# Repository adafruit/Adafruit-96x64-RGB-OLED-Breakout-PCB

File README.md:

# PCB for the Adafruit Mini Color OLED breakout board

<a href="http://www.adafruit.com/products/684"><br/>Click here to purchase one from the Adafruit shop</a>

We love our black and white monochrome displays but we also like to dabble with some color now and then. Our new 0.96" color OLED displays are perfect when you need an ultra-small display with vivid, high-contrast 16-bit color. The visible portion of the OLED measures 0.96" diagonal and contains 96x64 RGB pixels, each one made of red, green and blue OLEDs. Each pixel can be set with 16-bits of resolution for a large range of colors. Because the display uses OLEDs, there is no backlight, and the contrast is very high (black is really black). We picked this display for its excellent color, this is the nicest mini OLED we could find!

This OLED uses the SSD1331 driver chip, which manages the display. You can talk to the driver chip using either 4-wire write-only SPI (clock, data, chip select, data/command and an optional reset pin). Included on the fully assembled breakout is the OLED display and a small boost converter (required for providing 12V to the OLED) and a microSD card holder. New! We've updated this design to have built-in logic level shifting so you can use it with 3-5VDC power and logic levels. Our example code shows how to read a bitmap from the uSD card and display it all via SPI.

Of course, we wouldn't just leave you with a datasheet and a "good luck!" - [ we've written a full open source graphics library that can draw pixels, lines, rectangles, circles, text and bitmaps as well as example code and a wiring tutorial](http://learn.adafruit.com/096-mini-color-oled).
The code is written for Arduino but can be easily ported to your favorite microcontroller!

OLED Breakout Board - 16-bit Color 0.96" w/microSD holder ([4:55](https://www.youtube.com/watch?feature=player_detailpage&v=Cvf2_pIx7Aw#t=295))

## License

Adafruit invests time and resources providing this open source design, 
please support Adafruit and open-source hardware by purchasing 
products from Adafruit!

Designed by Adafruit Industries.  
Creative Commons Attribution, Share-Alike license, check license.txt for more information
All text above must be included in any redistribution

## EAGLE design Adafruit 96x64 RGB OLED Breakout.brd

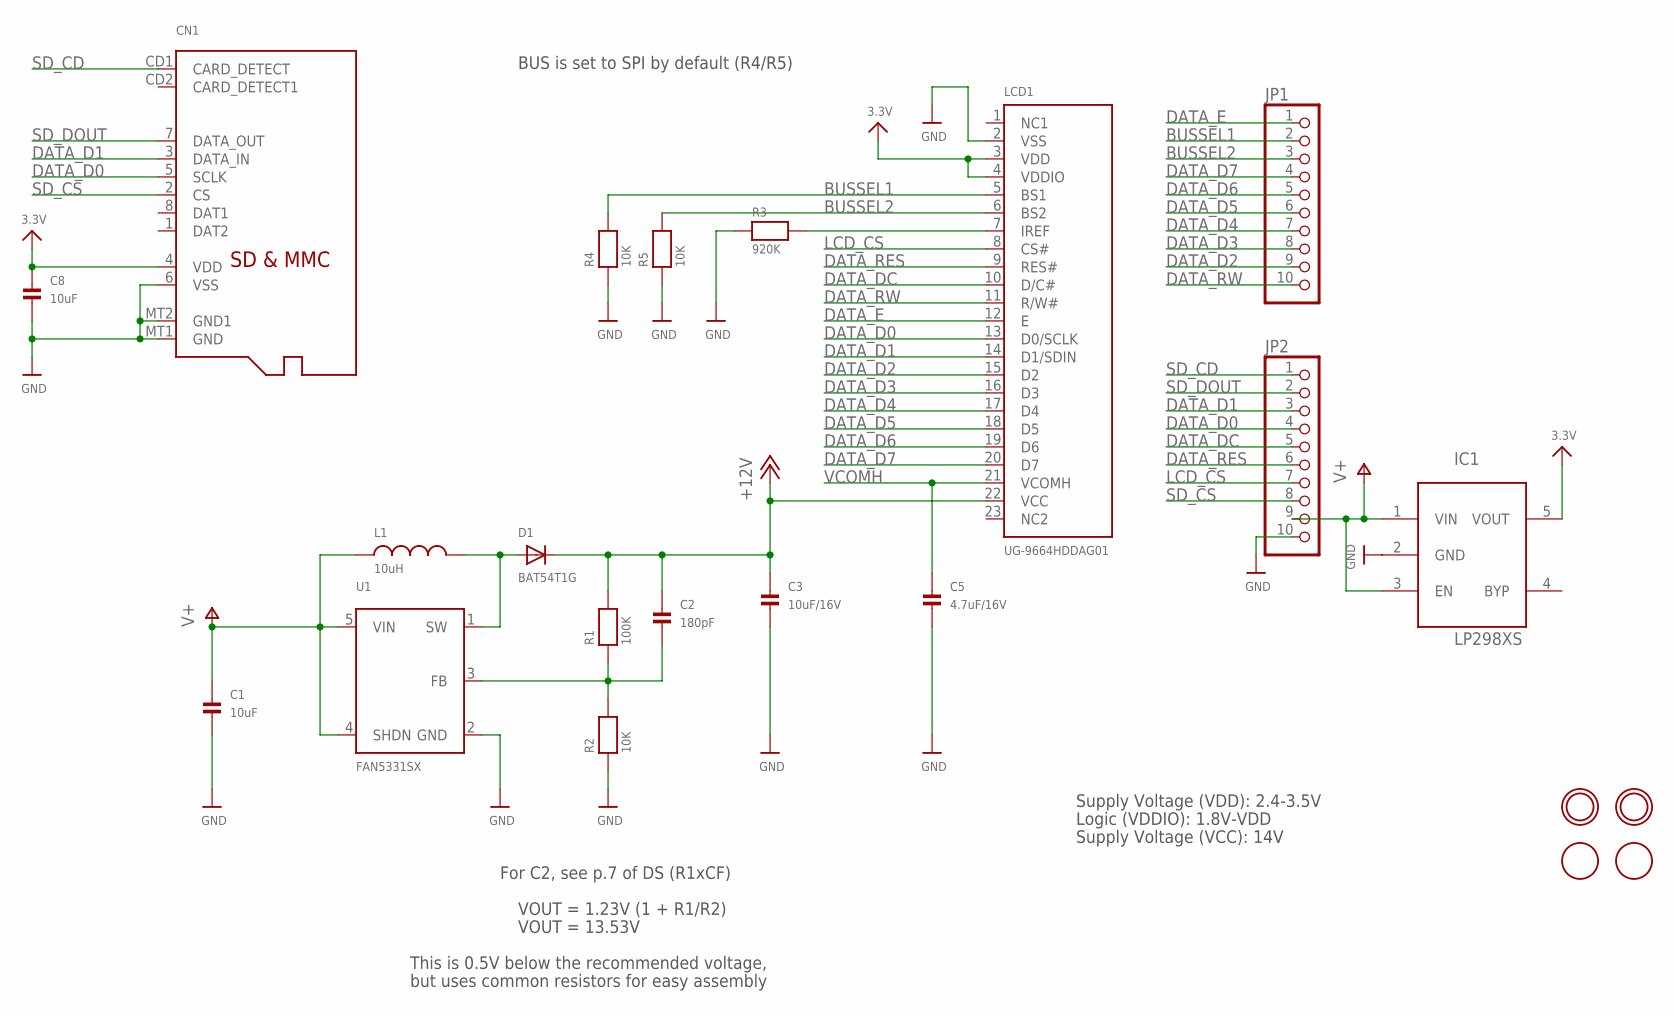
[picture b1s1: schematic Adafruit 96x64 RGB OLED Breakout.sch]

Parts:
C1, C8: 10uF; 0805
C2: 180pF; 0805
C3: 10uF/16V; 0805
C5: 4.7uF/16V; 0805
CN1: MICROSD
D1: BAT54T1G; SOD-123
IC1: LP298XS; SOT23-5L
JP1, JP2: HEADER-1X10THICKER; 1X10_ROUND_76
L1: 10uH; INDUCTOR_1007
LCD1: UG-9664HDDAG01; UG-9664HDDAG01_WRAPAROUND
R1: 100K; 0805
R2, R4, R5: 10K; 0805
R3: 920K; 0805
U1: FAN5331SX; SOT23-5
U$9, U$11: MOUNTINGHOLE2.0; MOUNTINGHOLE_2.0_PLATED
U$12, U$13: FIDUCIAL; FIDUCIAL_1MM

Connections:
3.3V: C8.1, CN1.4 (VDD), IC1.5 (VOUT), LCD1.3 (VDD), LCD1.4 (VDDIO)
+12V: C2.1, C3.1, D1.C, LCD1.22 (VCC), R1.2
BUSSEL1: JP1.2, LCD1.5 (BS1), R4.2
BUSSEL2: JP1.3, LCD1.6 (BS2), R5.2
DATA_D0: CN1.5 (SCLK), JP2.4, LCD1.13 (D0/SCLK)
DATA_D1: CN1.3 (DATA_IN), JP2.3, LCD1.14 (D1/SDIN)
DATA_D2: JP1.9, LCD1.15 (D2)
DATA_D3: JP1.8, LCD1.16 (D3)
DATA_D4: JP1.7, LCD1.17 (D4)
DATA_D5: JP1.6, LCD1.18 (D5)
DATA_D6: JP1.5, LCD1.19 (D6)
DATA_D7: JP1.4, LCD1.20 (D7)
DATA_DC: JP2.5, LCD1.10 (D/C#)
DATA_E: JP1.1, LCD1.12 (E)
DATA_RES: JP2.6, LCD1.9 (RES#)
DATA_RW: JP1.10, LCD1.11 (R/W#)
GND: C1.2, C3.2, C5.2, C8.2, CN1.6 (VSS), CN1.MT1 (GND), CN1.MT2 (GND1), IC1.2 (GND), JP2.10, LCD1.2 (VSS), R2.1, R3.1, R4.1, R5.1, U1.2 (GND)
LCD_CS: JP2.7, LCD1.8 (CS#)
unnamed: D1.A, L1.P$2 (2), U1.1 (SW)
unnamed: C2.2, R1.1, R2.2, U1.3 (FB)
unnamed: LCD1.7 (IREF), R3.2
SD_CD: CN1.CD1 (CARD_DETECT), JP2.1
SD_CS: CN1.2 (CS), JP2.8
SD_DOUT: CN1.7 (DATA_OUT), JP2.2
V+: C1.1, IC1.1 (VIN), IC1.3 (EN), JP2.9, L1.P$1 (1), U1.4 (SHDN), U1.5 (VIN)
VCOMH: C5.1, LCD1.21 (VCOMH)

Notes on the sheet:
Supply Voltage (VDD): 2.4-3.5V
Logic (VDDIO): 1.8V-VDD
Supply Voltage (VCC): 14V
For C2, see p.7 of DS (R1xCF)
VOUT = 1.23V (1 + R1/R2)
VOUT = 13.53V
This is 0.5V below the recommended voltage,
but uses common resistors for easy assembly
BUS is set to SPI by default (R4/R5)

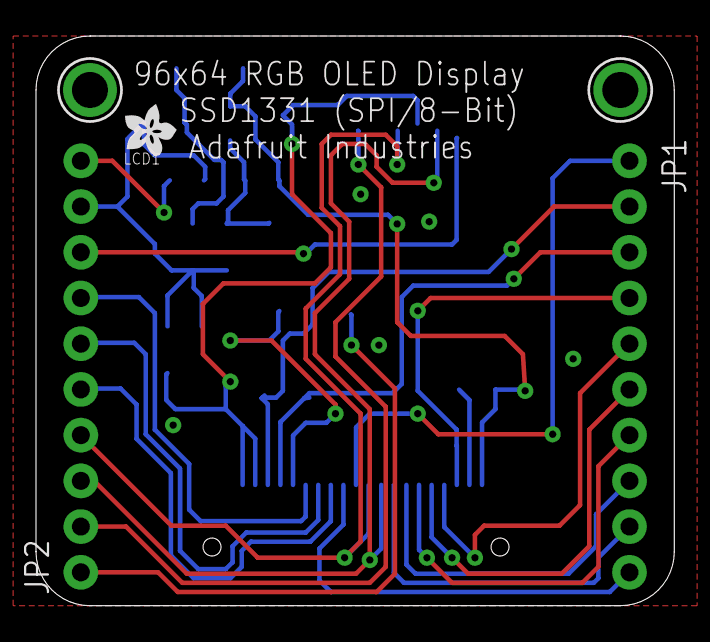
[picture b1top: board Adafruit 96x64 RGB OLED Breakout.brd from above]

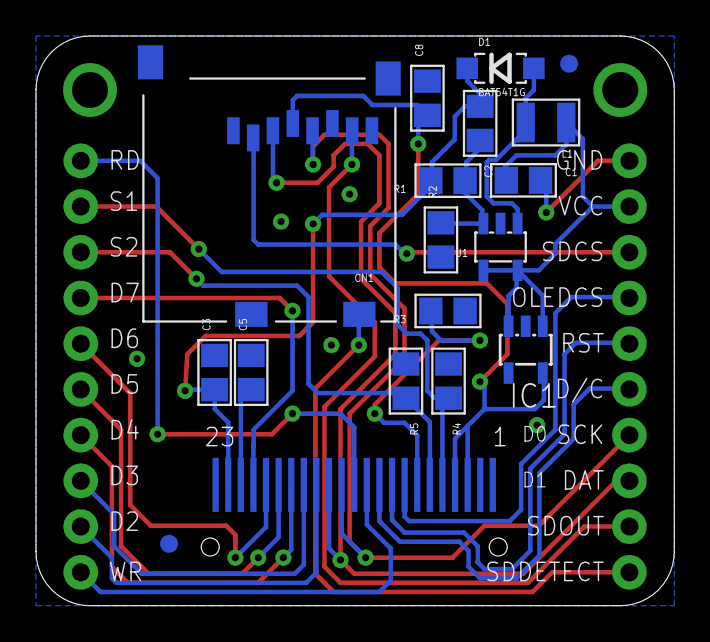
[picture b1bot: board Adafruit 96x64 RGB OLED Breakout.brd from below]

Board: 2 copper layers, 35.5 x 31.6 mm, 23 parts (17 on the bottom side), 26 nets.

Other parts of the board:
U$22: ADAFRUIT200MIL

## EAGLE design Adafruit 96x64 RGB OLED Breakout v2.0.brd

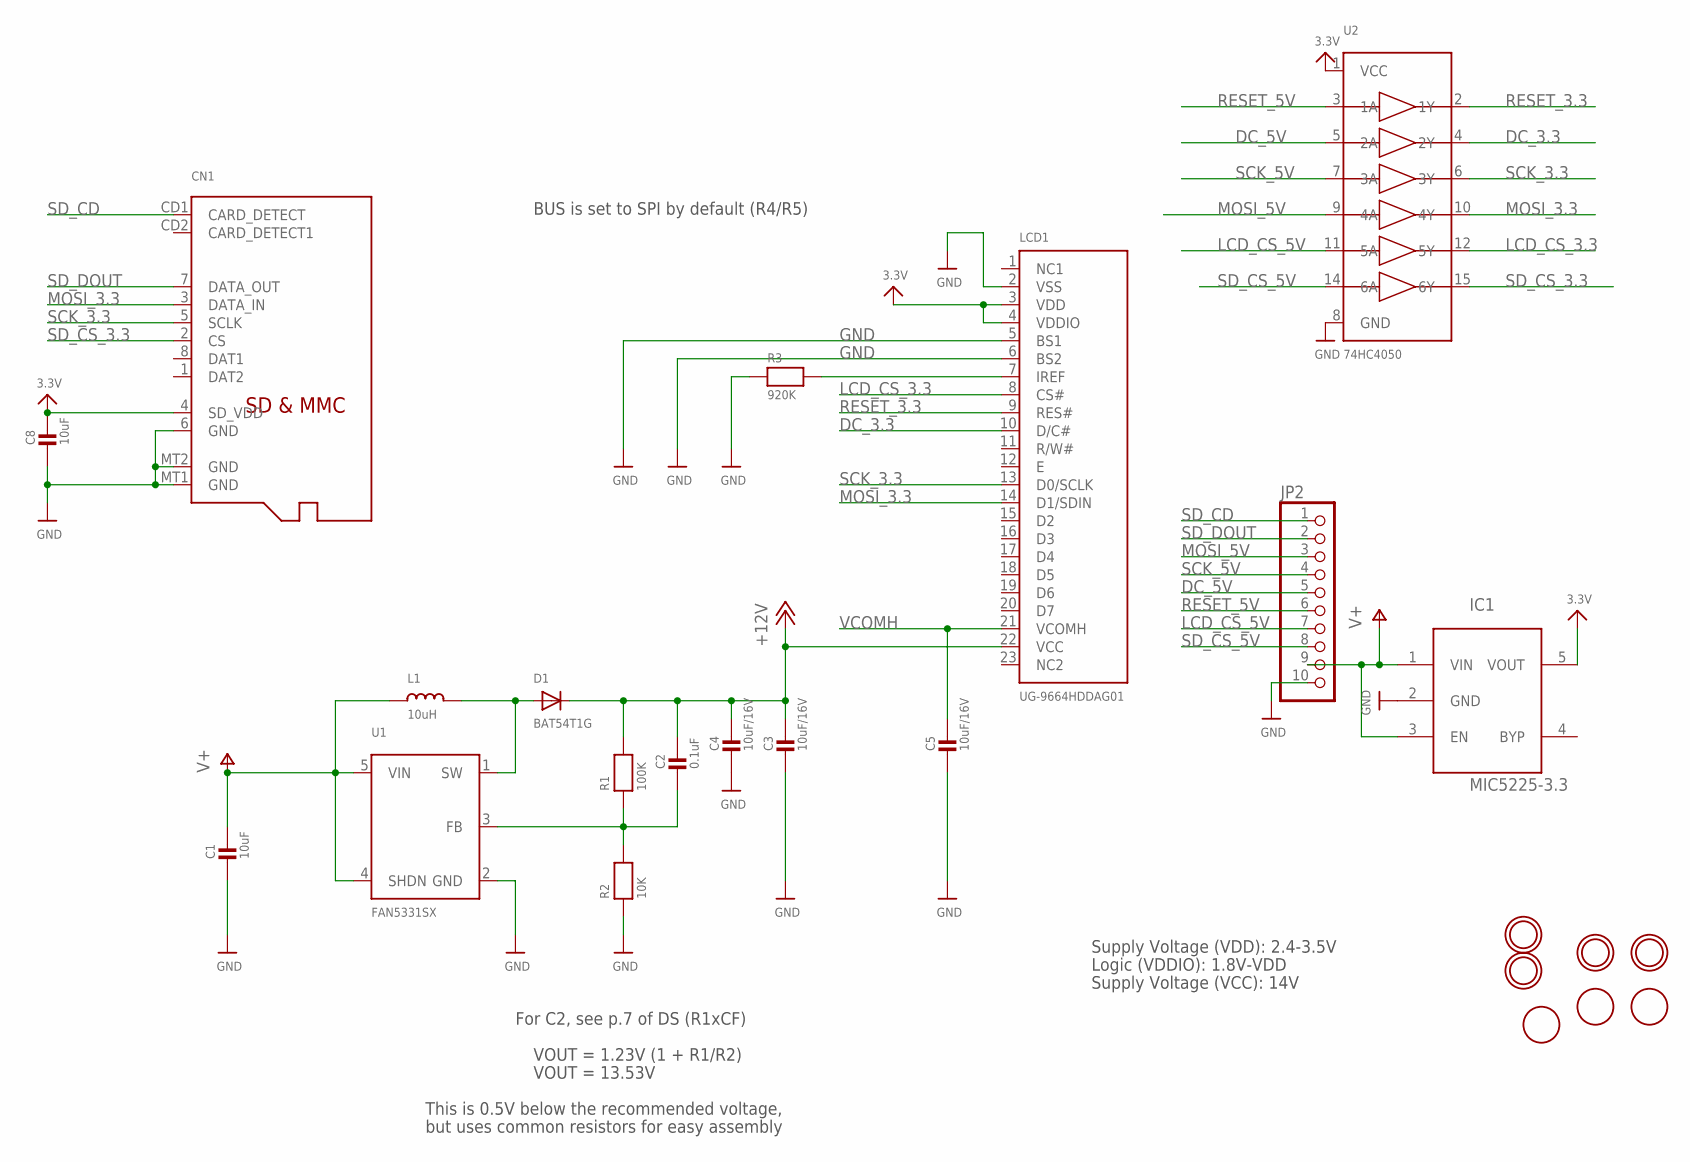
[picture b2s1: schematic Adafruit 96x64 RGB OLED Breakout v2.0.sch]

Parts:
C1, C8: 10uF; 0805
C2: 0.1uF; 0805
C3, C4, C5: 10uF/16V; 0805
CN1: MICROSD
D1: BAT54T1G; SOD-123
IC1: MIC5225-3.3; SOT23-5L
JP2: HEADER-1X10THICKER; 1X10_ROUND_76
L1: 10uH; INDUCTOR_1007
LCD1: UG-9664HDDAG01; UG-9664HDDAG01_WRAPAROUND
R1: 100K; 0805
R2: 10K; 0805
R3: 920K; 0805
U1: FAN5331SX; SOT23-5
U2: 74HC4050; SOIC16
U$9, U$10, U$11, U$15: MOUNTINGHOLE2.5; MOUNTINGHOLE_2.5_PLATED
U$12, U$13, U$16: FIDUCIAL; FIDUCIAL_1MM

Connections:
3.3V: C8.1, CN1.4 (SD_VDD), IC1.5 (VOUT), LCD1.3 (VDD), LCD1.4 (VDDIO), U2.1 (VCC)
+12V: C2.1, C3.1, C4.1, D1.C, LCD1.22 (VCC), R1.2
DC_3.3: LCD1.10 (D/C#), U2.4 (2Y)
DC_5V: JP2.5, U2.5 (2A)
GND: C1.2, C3.2, C4.2, C5.2, C8.2, CN1.6 (GND), CN1.MT1 (GND), CN1.MT2 (GND), IC1.2 (GND), JP2.10, LCD1.2 (VSS), LCD1.5 (BS1), LCD1.6 (BS2), R2.1, R3.1, U1.2 (GND), U2.8 (GND)
LCD_CS_3.3: LCD1.8 (CS#), U2.12 (5Y)
LCD_CS_5V: JP2.7, U2.11 (5A)
MOSI_3.3: CN1.3 (DATA_IN), LCD1.14 (D1/SDIN), U2.10 (4Y)
MOSI_5V: JP2.3, U2.9 (4A)
unnamed: D1.A, L1.P$2 (2), U1.1 (SW)
unnamed: C2.2, R1.1, R2.2, U1.3 (FB)
unnamed: LCD1.7 (IREF), R3.2
RESET_3.3: LCD1.9 (RES#), U2.2 (1Y)
RESET_5V: JP2.6, U2.3 (1A)
SCK_3.3: CN1.5 (SCLK), LCD1.13 (D0/SCLK), U2.6 (3Y)
SCK_5V: JP2.4, U2.7 (3A)
SD_CD: CN1.CD1 (CARD_DETECT), JP2.1
SD_CS_3.3: CN1.2 (CS), U2.15 (6Y)
SD_CS_5V: JP2.8, U2.14 (6A)
SD_DOUT: CN1.7 (DATA_OUT), JP2.2
V+: C1.1, IC1.1 (VIN), IC1.3 (EN), JP2.9, L1.P$1 (1), U1.4 (SHDN), U1.5 (VIN)
VCOMH: C5.1, LCD1.21 (VCOMH)

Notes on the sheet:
Supply Voltage (VDD): 2.4-3.5V
Logic (VDDIO): 1.8V-VDD
Supply Voltage (VCC): 14V
For C2, see p.7 of DS (R1xCF)
VOUT = 1.23V (1 + R1/R2)
VOUT = 13.53V
This is 0.5V below the recommended voltage,
but uses common resistors for easy assembly
BUS is set to SPI by default (R4/R5)

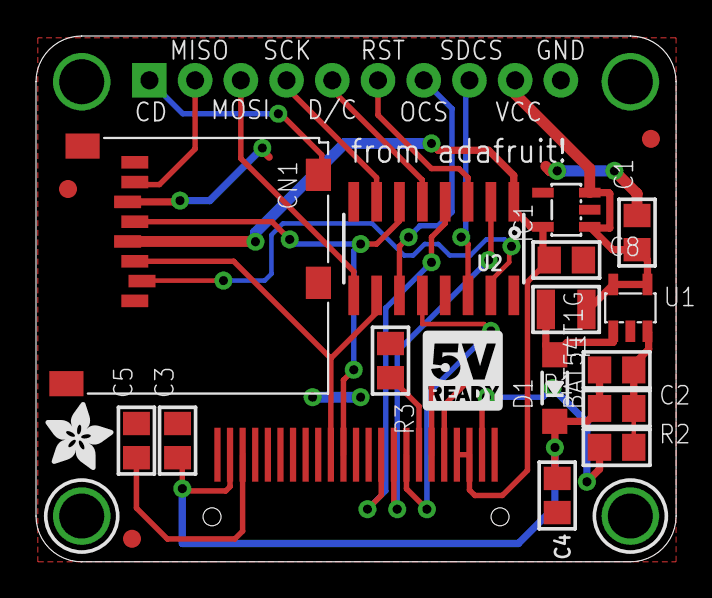
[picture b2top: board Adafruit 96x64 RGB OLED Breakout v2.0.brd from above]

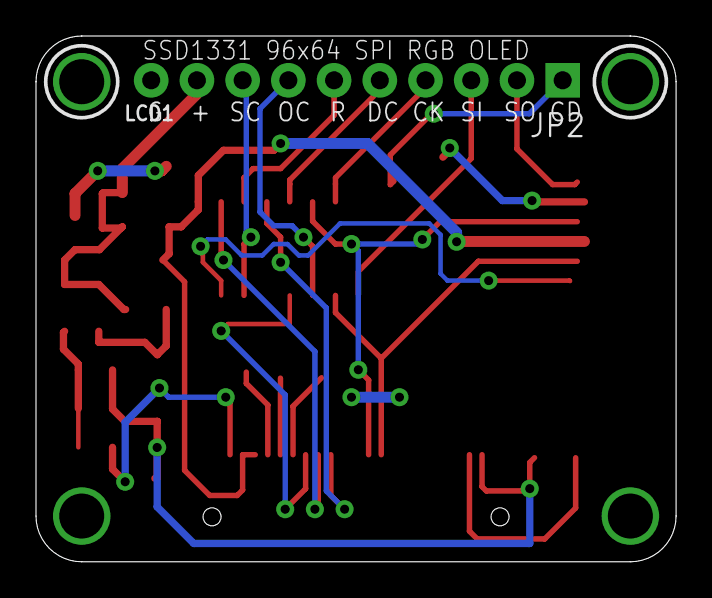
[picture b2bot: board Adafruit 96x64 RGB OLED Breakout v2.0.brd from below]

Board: 2 copper layers, 35.6 x 29.2 mm, 26 parts (4 on the bottom side), 22 nets.

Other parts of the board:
U$17: ADAFRUIT_3.5MM
U$28: LOGIC_5VREADY_5MM

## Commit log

2012-03-08 v0.3 with fixed S1/S2 silkscreen
2012-03-08 read!
2014-04-17 v2 (SPI only)
2019-05-07 readme + image
2019-05-16 added license.txt
2026-06-03 update file format to XML
